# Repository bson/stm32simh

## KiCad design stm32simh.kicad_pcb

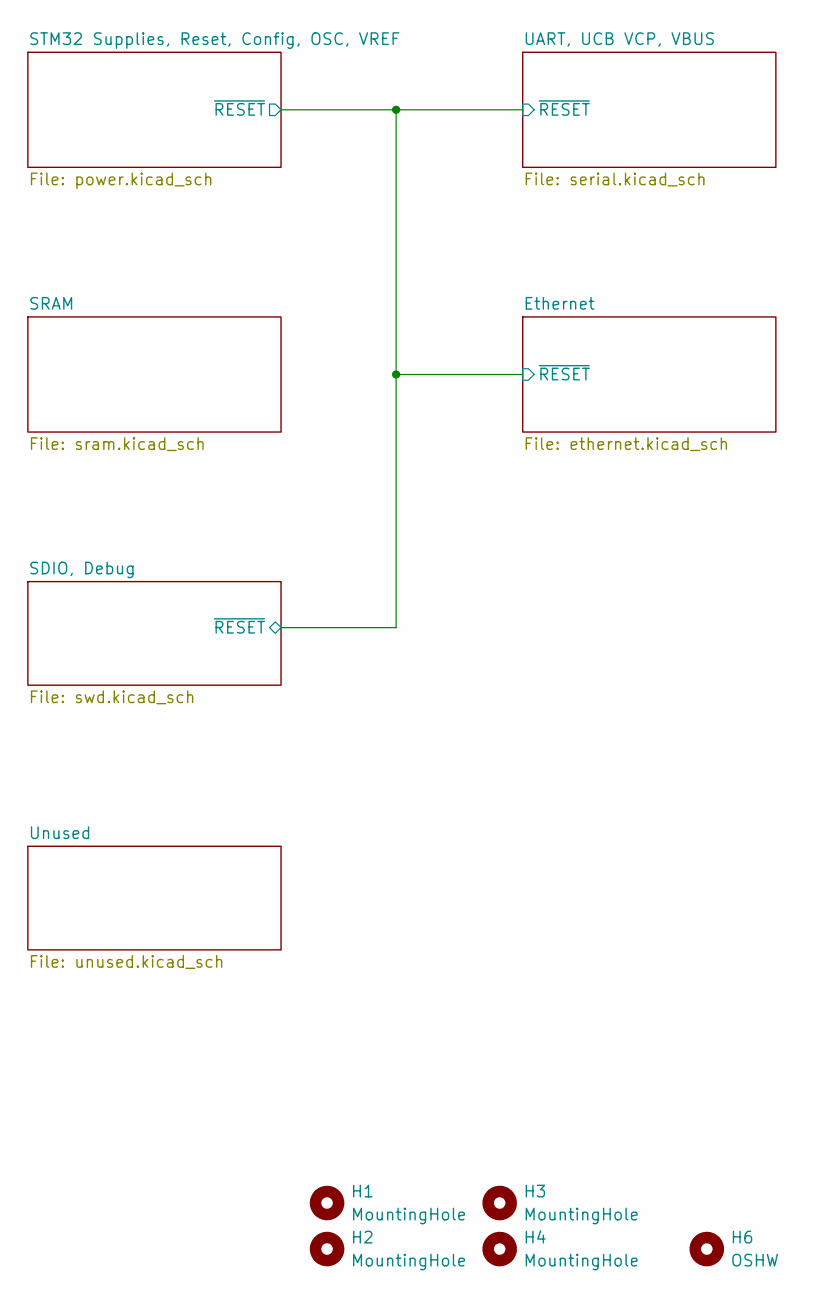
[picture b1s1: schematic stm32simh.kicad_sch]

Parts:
H1, H2, H3, H4: MountingHole; MountingHole_2.2mm_M2_ISO14580_Pad
H6: OSHW; OSHW-Logo_7.5x8mm_SilkScreen

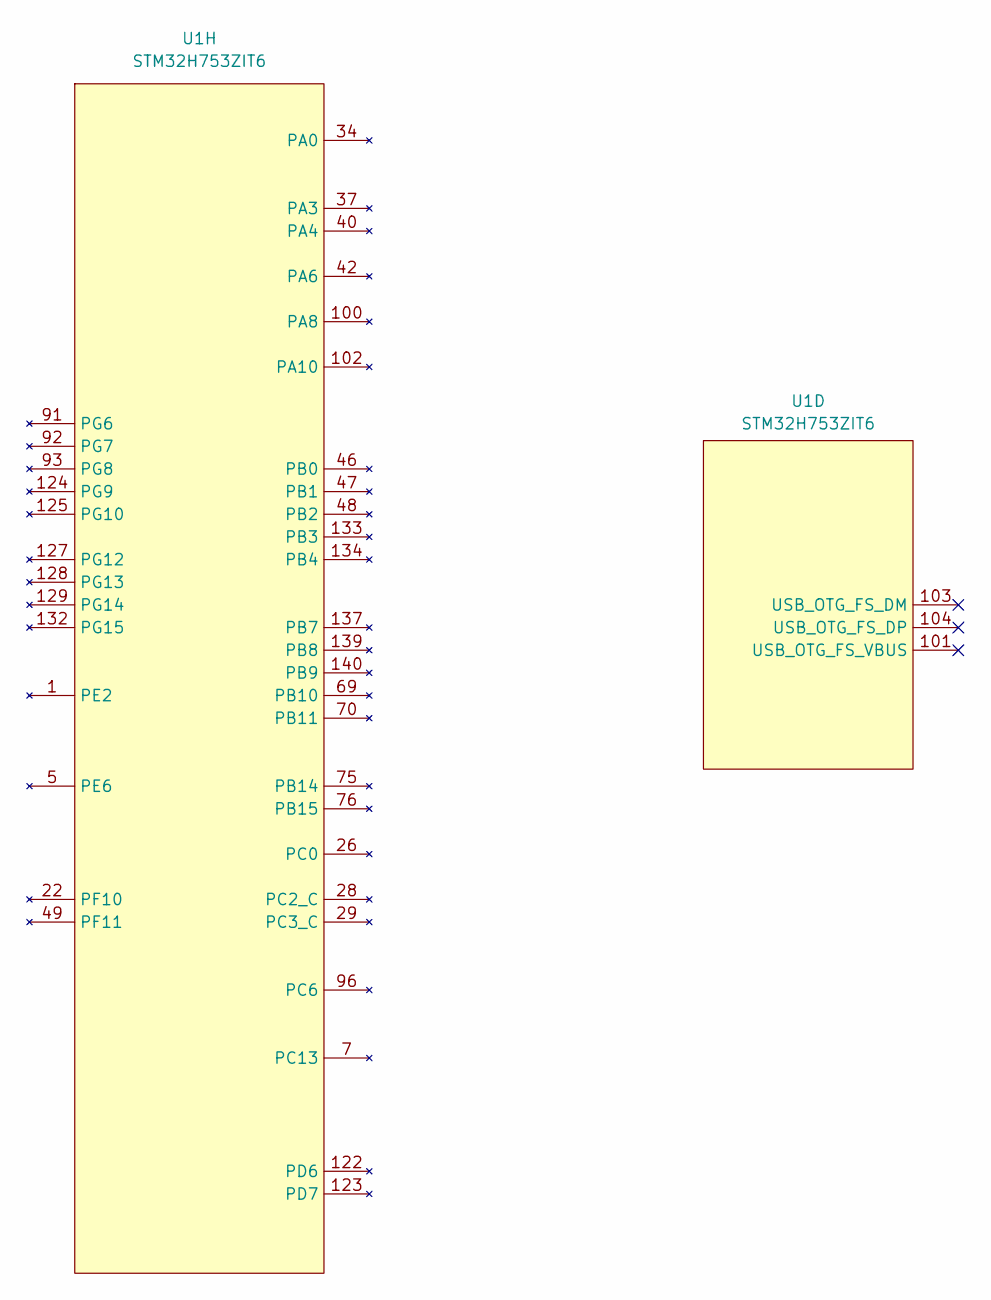
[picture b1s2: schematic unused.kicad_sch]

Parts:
U1: STM32H753ZIT6; LQFP-144_20x20mm_P0.5mm; MPN STM32H753ZIT6

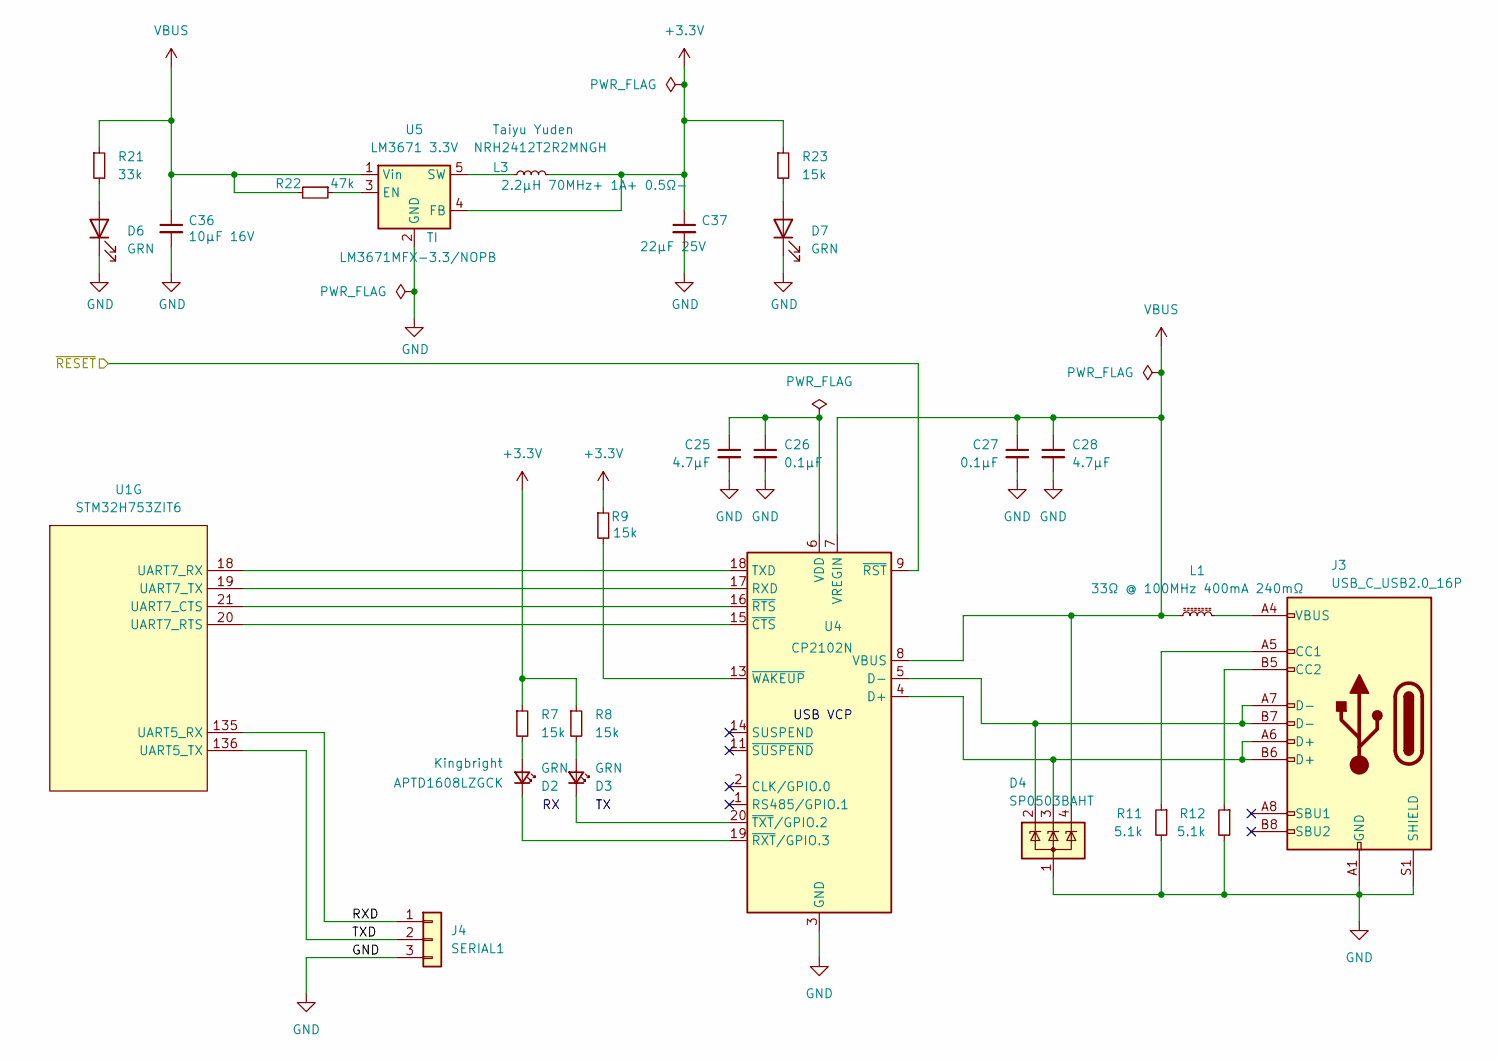
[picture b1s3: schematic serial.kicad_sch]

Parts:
C25, C28: 4.7µF; C_0805_2012Metric; LCSC C84718
C26, C27: 0.1µF; C_0402_1005Metric; LCSC C3012376
C36: 10µF 16V; C_0603_1608Metric; LCSC C109457
C37: 22µF 25V; C_0805_2012Metric; LCSC C258782
D2, D3: GRN; D_0603_1608Metric; MPN APTD1608LZGCK; LCSC C5246833
D4: SP0503BAHT; SOT-143; LCSC C5337181
D6, D7: GRN; D_0603_1608Metric; LCSC C5246833
J3: USB_C_USB2.0_16P; USB_C_Receptacle_HCTL_HC-TYPE-C-16P-01A; LCSC C2909599
J4: SERIAL1; PinHeader_1x03_P2.54mm_Vertical
L1: 33Ω @ 100MHz 400mA 240mΩ; L_0402_1005Metric; MPN MMZ1005D330CTD25
L3: 2.2µH 70MHz+ 1A+ 0.5Ω-; L_Taiyo-Yuden_NR-24xx; Part NRH2412T2R2MNGH
R7, R8, R23: 15k; R_0402_1005Metric; LCSC C850820
R9: 15k; R_0402_1005Metric; LCSC C375970
R11, R12: 5.1k; R_0402_1005Metric; LCSC C384321
R21: 33k; R_0402_1005Metric; LCSC C2906928
R22: 47k; R_0402_1005Metric; LCSC C3017507
U1: STM32H753ZIT6; LQFP-144_20x20mm_P0.5mm; MPN STM32H753ZIT6
U4: CP2102N; CP2102N-QFN20; LCSC C969913
U5: LM3671 3.3V; TSOT-23-5; Part LM3671MFX-3.3/NOPB; LCSC C201586

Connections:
+3.3V: C37.1, L3.2, R7.1, R8.1, R9.1, R23.1, U5.4 (FB); also elsewhere on the board
/Ethernet/~RESET: U4.9 (~RST); also elsewhere on the board
/UART, UCB VCP, VBUS/RXD: J4.1, U1.135 (UART5_RX)
/UART, UCB VCP, VBUS/TXD: J4.2, U1.136 (UART5_TX)
GND: C25.2, C26.2, C27.2, C28.2, C36.2, C37.2, D4.1 (A), D6.1 (K), D7.1 (K), J3.A1 (GND), J3.A12 (GND), J3.B1 (GND), J3.B12 (GND), J3.S1 (SHIELD), J4.3, R11.2, R12.2, U4.3 (GND), U4.12 (GND), U4.21 (GND), U5.2 (GND); also elsewhere on the board
unnamed: D2.2 (A), R7.2
unnamed: D2.1 (K), U4.19 (~RXT/GPIO.3)
unnamed: D3.2 (A), R8.2
unnamed: D3.1 (K), U4.20 (~TXT/GPIO.2)
unnamed: D6.2 (A), R21.2
unnamed: D7.2 (A), R23.2
unnamed: J3.A5 (CC1), R11.1
unnamed: J3.B5 (CC2), R12.1
unnamed: J3.A4 (VBUS), J3.A9 (VBUS), J3.B4 (VBUS), J3.B9 (VBUS), L1.2
unnamed: U1.21 (UART7_CTS), U4.16 (~RTS)
unnamed: U1.20 (UART7_RTS), U4.15 (~CTS)
unnamed: U1.18 (UART7_RX), U4.18 (TXD)
unnamed: U1.19 (UART7_TX), U4.17 (RXD)
unnamed: D4.3 (K), J3.A6 (D+), J3.B6 (D+), U4.4 (D+)
unnamed: D4.2 (K), J3.A7 (D-), J3.B7 (D-), U4.5 (D-)
unnamed: C25.1, C26.1, U4.6 (VDD)
unnamed: R9.2, U4.13 (~WAKEUP)
unnamed: R22.1, U5.3 (EN)
unnamed: L3.1, U5.5 (SW)
VBUS: C27.1, C28.1, C36.1, D4.4 (K), L1.1, R21.1, R22.2, U4.7 (VREGIN), U4.8 (VBUS), U5.1 (Vin)

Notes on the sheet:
USB VCP

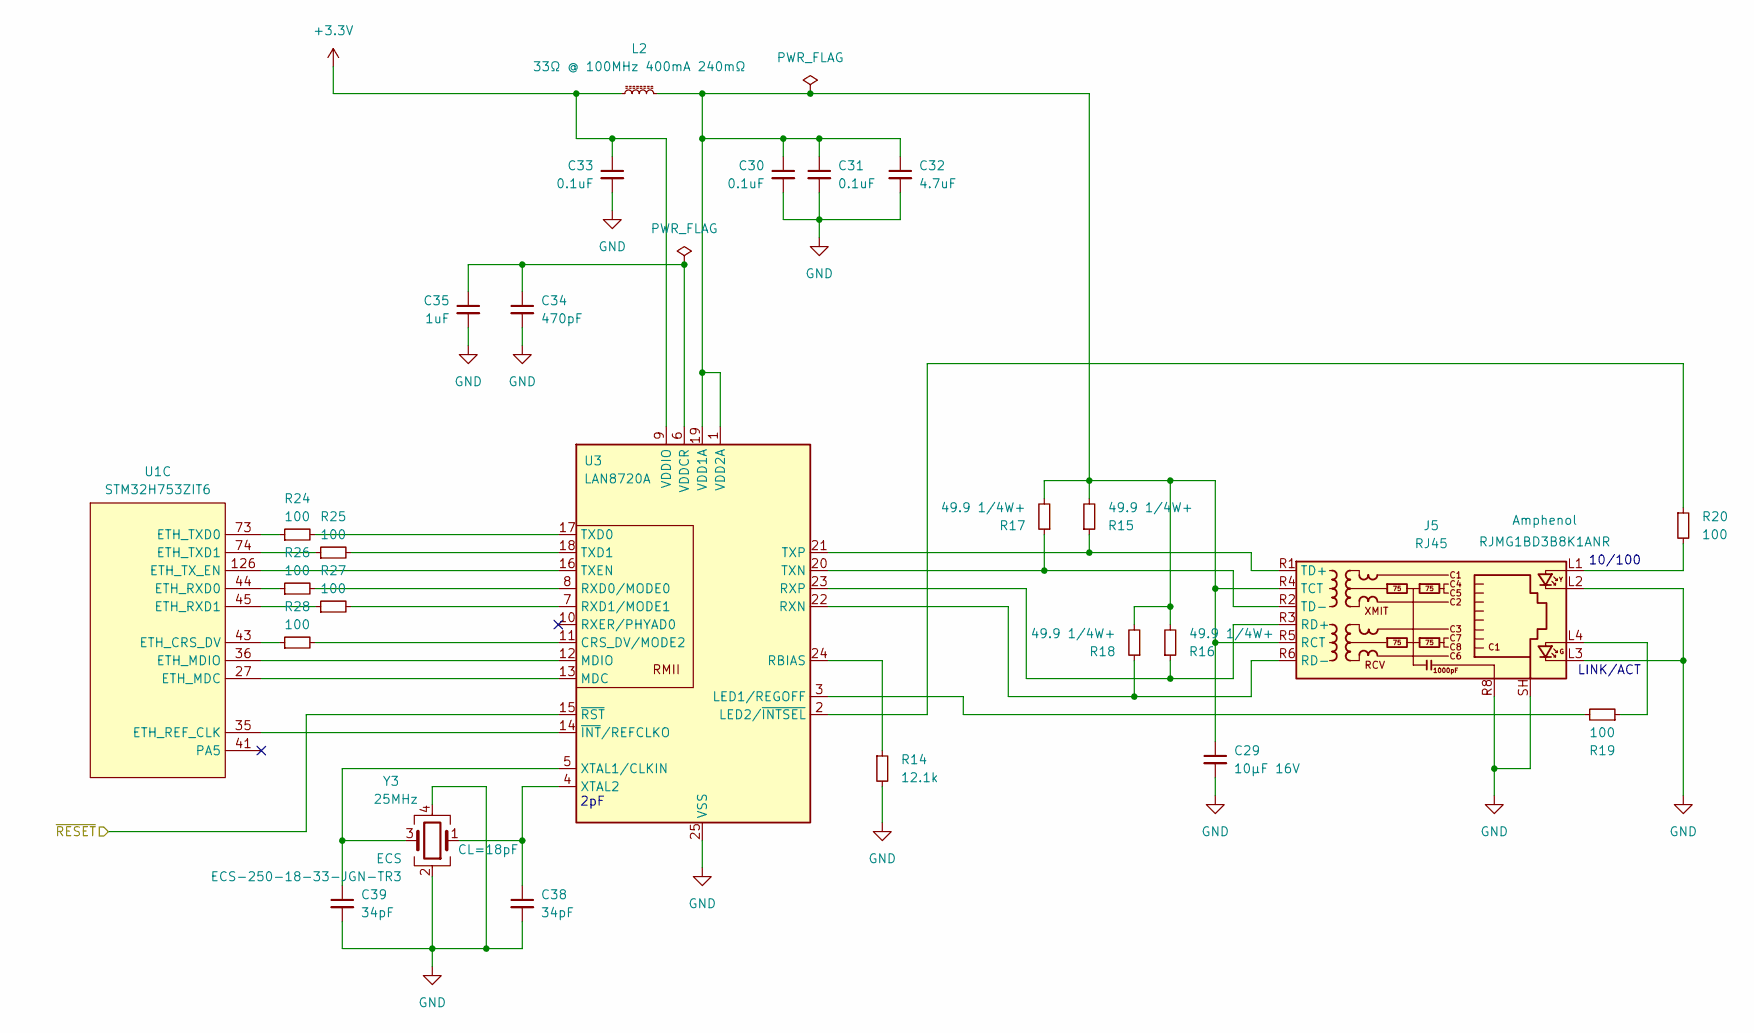
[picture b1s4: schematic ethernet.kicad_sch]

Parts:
C29: 10µF 16V; C_0603_1608Metric; LCSC C109457
C30, C31, C33: 0.1uF; C_0402_1005Metric
C32: 4.7uF; C_0805_2012Metric
C34: 470pF; C_0402_1005Metric
C35: 1uF; C_0402_1005Metric
C38, C39: 34pF; C_0402_1005Metric
J5: RJ45; RJ45_Amphenol_RJMG1BD3B8K1ANR; Part RJMG1BD3B8K1ANR
L2: 33Ω @ 100MHz 400mA 240mΩ; L_0402_1005Metric; MPN MMZ1005D330CTD25
R14: 12.1k; R_0402_1005Metric
R15, R16, R17, R18: 49.9 1/4W+; R_0805_2012Metric; LCSC C4088942
R19, R20, R24, R25, R26, R27, R28: 100; R_0402_1005Metric; LCSC C453594
U1: STM32H753ZIT6; LQFP-144_20x20mm_P0.5mm; MPN STM32H753ZIT6
U3: LAN8720A; VQFN-24-1EP_4x4mm_P0.5mm_EP2.5x2.5mm
Y3: 25MHz; Crystal_SMD_3225-4Pin_3.2x2.5mm; Part ECS-250-18-33-JGN-TR3; LCSC C7294571

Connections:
+3.3V: C33.1, L2.1, U3.9 (VDDIO); also elsewhere on the board
/Ethernet/~RESET: U3.15 (~RST); also elsewhere on the board
GND: C29.2, C30.2, C31.2, C32.2, C33.2, C34.2, C35.2, C38.2, C39.2, J5.L2, J5.L3, J5.R8, J5.SH, R14.2, U3.25 (VSS), Y3.2, Y3.4; also elsewhere on the board
unnamed: J5.L1, R20.2
unnamed: J5.L4, R19.1
unnamed: C29.1, C30.1, C31.1, C32.1, J5.R4 (TCT), J5.R5 (RCT), L2.2, R15.2, R16.2, R17.2, R18.2, U3.1 (VDD2A), U3.19 (VDD1A)
unnamed: J5.R3 (RD+), R16.1, U3.23 (RXP)
unnamed: J5.R6 (RD-), R18.1, U3.22 (RXN)
unnamed: J5.R1 (TD+), R15.1, U3.21 (TXP)
unnamed: J5.R2 (TD-), R17.1, U3.20 (TXN)
unnamed: R28.1, U1.43 (ETH_CRS_DV)
unnamed: U1.27 (ETH_MDC), U3.13 (MDC)
unnamed: U1.36 (ETH_MDIO), U3.12 (MDIO)
unnamed: U1.35 (ETH_REF_CLK), U3.14 (~INT/REFCLKO)
unnamed: R26.1, U1.44 (ETH_RXD0)
unnamed: R27.1, U1.45 (ETH_RXD1)
unnamed: R24.1, U1.73 (ETH_TXD0)
unnamed: R25.1, U1.74 (ETH_TXD1)
unnamed: U1.126 (ETH_TX_EN), U3.16 (TXEN)
unnamed: R28.2, U3.11 (CRS_DV/MODE2)
unnamed: R19.2, U3.3 (LED1/REGOFF)
unnamed: R20.1, U3.2 (LED2/~INTSEL)
unnamed: R14.1, U3.24 (RBIAS)
unnamed: R26.2, U3.8 (RXD0/MODE0)
unnamed: R27.2, U3.7 (RXD1/MODE1)
unnamed: R24.2, U3.17 (TXD0)
unnamed: R25.2, U3.18 (TXD1)
unnamed: C34.1, C35.1, U3.6 (VDDCR)
unnamed: C39.1, U3.5 (XTAL1/CLKIN), Y3.3
unnamed: C38.1, U3.4 (XTAL2), Y3.1

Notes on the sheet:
LINK/ACT
2pF
10/100

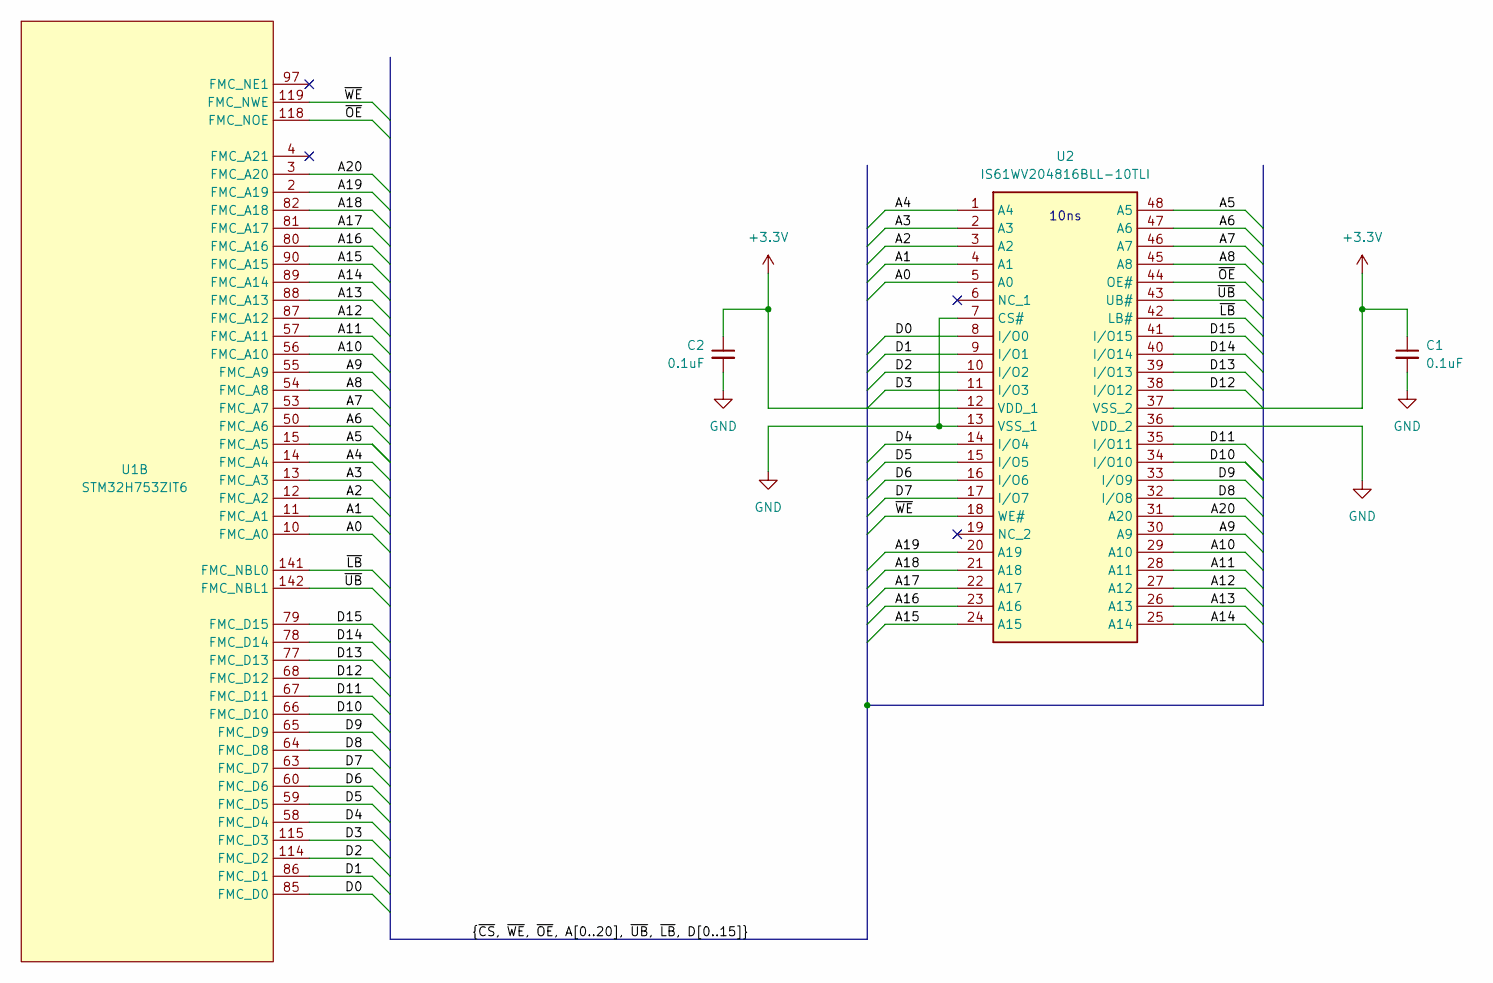
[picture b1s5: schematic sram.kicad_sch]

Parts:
C1, C2: 0.1uF; C_0402_1005Metric
U1: STM32H753ZIT6; LQFP-144_20x20mm_P0.5mm; MPN STM32H753ZIT6
U2: IS61WV204816BLL-10TLI; SOP50P2000X120-48N; Mouser Part Number 870-WV204816BLL10TLI

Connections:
+3.3V: C1.1, C2.1, U2.12 (VDD_1), U2.37 (VSS_2); also elsewhere on the board
/SRAM/A0: U1.10 (FMC_A0), U2.5 (A0)
/SRAM/A1: U1.11 (FMC_A1), U2.4 (A1)
/SRAM/A2: U1.12 (FMC_A2), U2.3 (A2)
/SRAM/A3: U1.13 (FMC_A3), U2.2 (A3)
/SRAM/A4: U1.14 (FMC_A4), U2.1 (A4)
/SRAM/A5: U1.15 (FMC_A5), U2.48 (A5)
/SRAM/A6: U1.50 (FMC_A6), U2.47 (A6)
/SRAM/A7: U1.53 (FMC_A7), U2.46 (A7)
/SRAM/A8: U1.54 (FMC_A8), U2.45 (A8)
/SRAM/A9: U1.55 (FMC_A9), U2.30 (A9)
/SRAM/A10: U1.56 (FMC_A10), U2.29 (A10)
/SRAM/A11: U1.57 (FMC_A11), U2.28 (A11)
/SRAM/A12: U1.87 (FMC_A12), U2.27 (A12)
/SRAM/A13: U1.88 (FMC_A13), U2.26 (A13)
/SRAM/A14: U1.89 (FMC_A14), U2.25 (A14)
/SRAM/A15: U1.90 (FMC_A15), U2.24 (A15)
/SRAM/A16: U1.80 (FMC_A16), U2.23 (A16)
/SRAM/A17: U1.81 (FMC_A17), U2.22 (A17)
/SRAM/A18: U1.82 (FMC_A18), U2.21 (A18)
/SRAM/A19: U1.2 (FMC_A19), U2.20 (A19)
/SRAM/A20: U1.3 (FMC_A20), U2.31 (A20)
/SRAM/D0: U1.85 (FMC_D0), U2.8 (I/O0)
/SRAM/D1: U1.86 (FMC_D1), U2.9 (I/O1)
/SRAM/D2: U1.114 (FMC_D2), U2.10 (I/O2)
/SRAM/D3: U1.115 (FMC_D3), U2.11 (I/O3)
/SRAM/D4: U1.58 (FMC_D4), U2.14 (I/O4)
/SRAM/D5: U1.59 (FMC_D5), U2.15 (I/O5)
/SRAM/D6: U1.60 (FMC_D6), U2.16 (I/O6)
/SRAM/D7: U1.63 (FMC_D7), U2.17 (I/O7)
/SRAM/D8: U1.64 (FMC_D8), U2.32 (I/O8)
/SRAM/D9: U1.65 (FMC_D9), U2.33 (I/O9)
/SRAM/D10: U1.66 (FMC_D10), U2.34 (I/O10)
/SRAM/D11: U1.67 (FMC_D11), U2.35 (I/O11)
/SRAM/D12: U1.68 (FMC_D12), U2.38 (I/O12)
/SRAM/D13: U1.77 (FMC_D13), U2.39 (I/O13)
/SRAM/D14: U1.78 (FMC_D14), U2.40 (I/O14)
/SRAM/D15: U1.79 (FMC_D15), U2.41 (I/O15)
/SRAM/~LB: U1.141 (FMC_NBL0), U2.42 (LB#)
/SRAM/~OE: U1.118 (FMC_NOE), U2.44 (OE#)
/SRAM/~UB: U1.142 (FMC_NBL1), U2.43 (UB#)
/SRAM/~WE: U1.119 (FMC_NWE), U2.18 (WE#)
GND: C1.2, C2.2, U2.7 (CS#), U2.13 (VSS_1), U2.36 (VDD_2); also elsewhere on the board

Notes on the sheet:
10ns

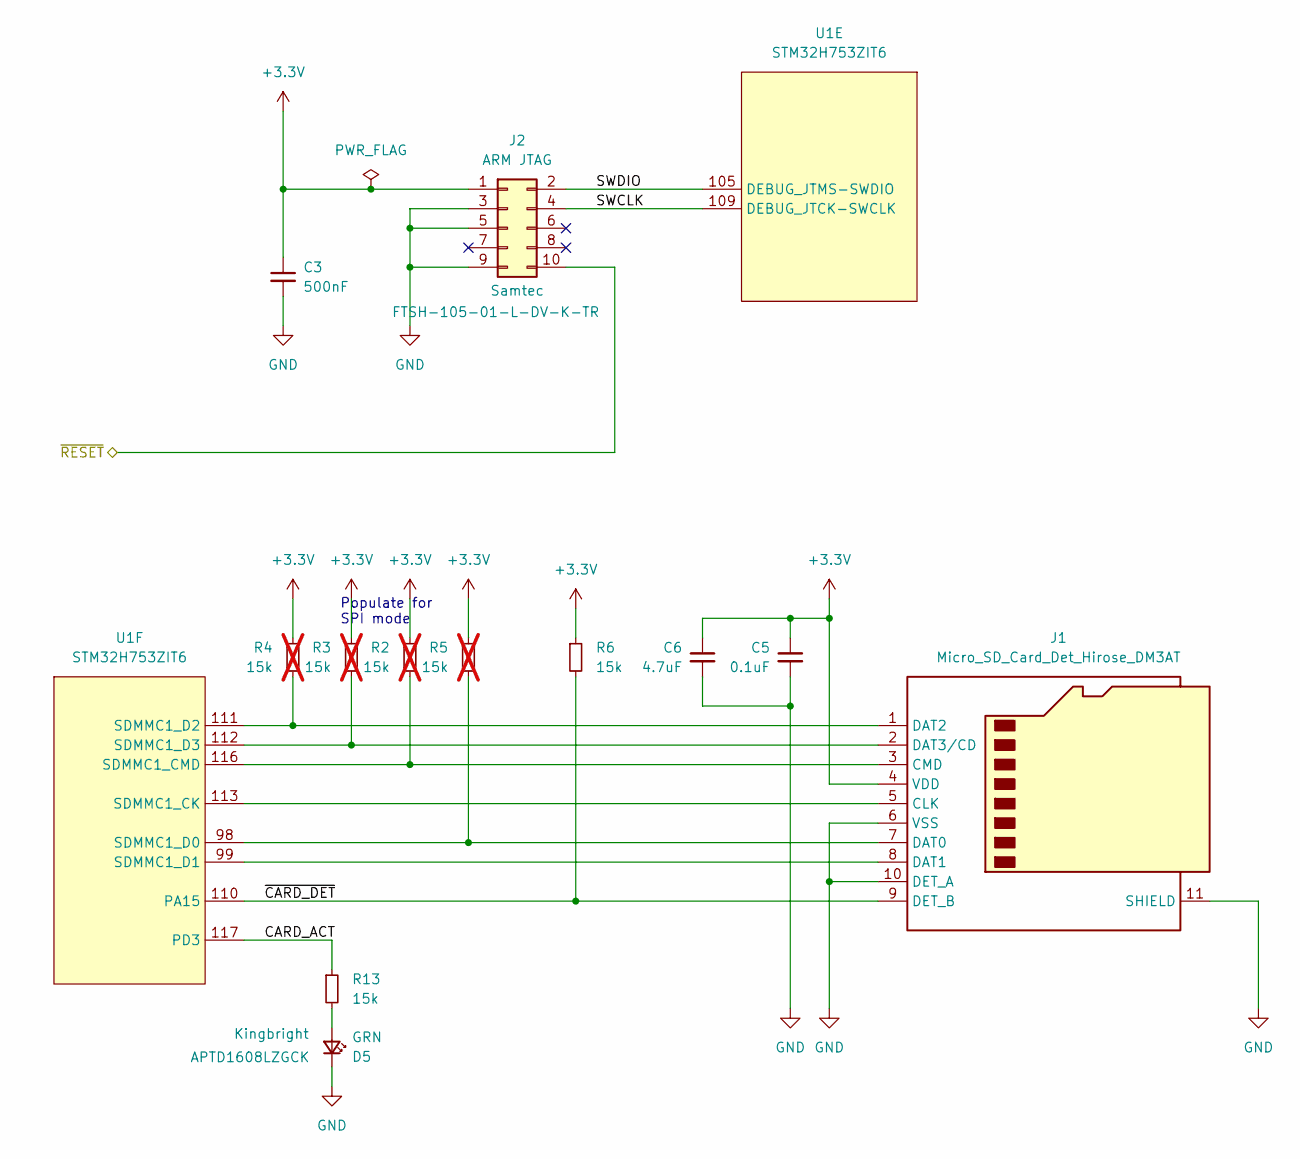
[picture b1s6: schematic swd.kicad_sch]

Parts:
C3: 500nF; C_0402_1005Metric
C5: 0.1uF; C_0402_1005Metric
C6: 4.7uF; C_0805_2012Metric
D5: GRN; D_0603_1608Metric; MPN APTD1608LZGCK; LCSC C5246833
J1: Micro_SD_Card_Det_Hirose_DM3AT; microSD_HC_Hirose_DM3AT-SF-PEJM5
J2: ARM JTAG; SOIC-10_3.9x4.9mm_P1mm; MPN FTSH-105-01-L-DV-K-TR
R2, R3, R4, R5: 15k; R_0402_1005Metric; not fitted
R6: 15k; R_0402_1005Metric
R13: 15k; R_0402_1005Metric; LCSC C850820
U1: STM32H753ZIT6; LQFP-144_20x20mm_P0.5mm; MPN STM32H753ZIT6

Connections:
+3.3V: C3.1, C5.1, C6.1, J1.4 (VDD), J2.1, R2.1, R3.1, R4.1, R5.1, R6.1; also elsewhere on the board
/Ethernet/~RESET: J2.10; also elsewhere on the board
/SDIO, Debug/CARD_ACT: R13.1, U1.117 (PD3)
/SDIO, Debug/SWCLK: J2.4, U1.109 (DEBUG_JTCK-SWCLK)
/SDIO, Debug/SWDIO: J2.2, U1.105 (DEBUG_JTMS-SWDIO)
/SDIO, Debug/~CARD_DET: J1.9 (DET_B), R6.2, U1.110 (PA15)
GND: C3.2, C5.2, C6.2, D5.1 (K), J1.6 (VSS), J1.10 (DET_A), J1.11 (SHIELD), J2.3, J2.5, J2.9; also elsewhere on the board
unnamed: D5.2 (A), R13.2
unnamed: J1.5 (CLK), U1.113 (SDMMC1_CK)
unnamed: J1.3 (CMD), R2.2, U1.116 (SDMMC1_CMD)
unnamed: J1.7 (DAT0), R5.2, U1.98 (SDMMC1_D0)
unnamed: J1.8 (DAT1), U1.99 (SDMMC1_D1)
unnamed: J1.1 (DAT2), R4.2, U1.111 (SDMMC1_D2)
unnamed: J1.2 (DAT3/CD), R3.2, U1.112 (SDMMC1_D3)

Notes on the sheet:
Populate for SPI mode

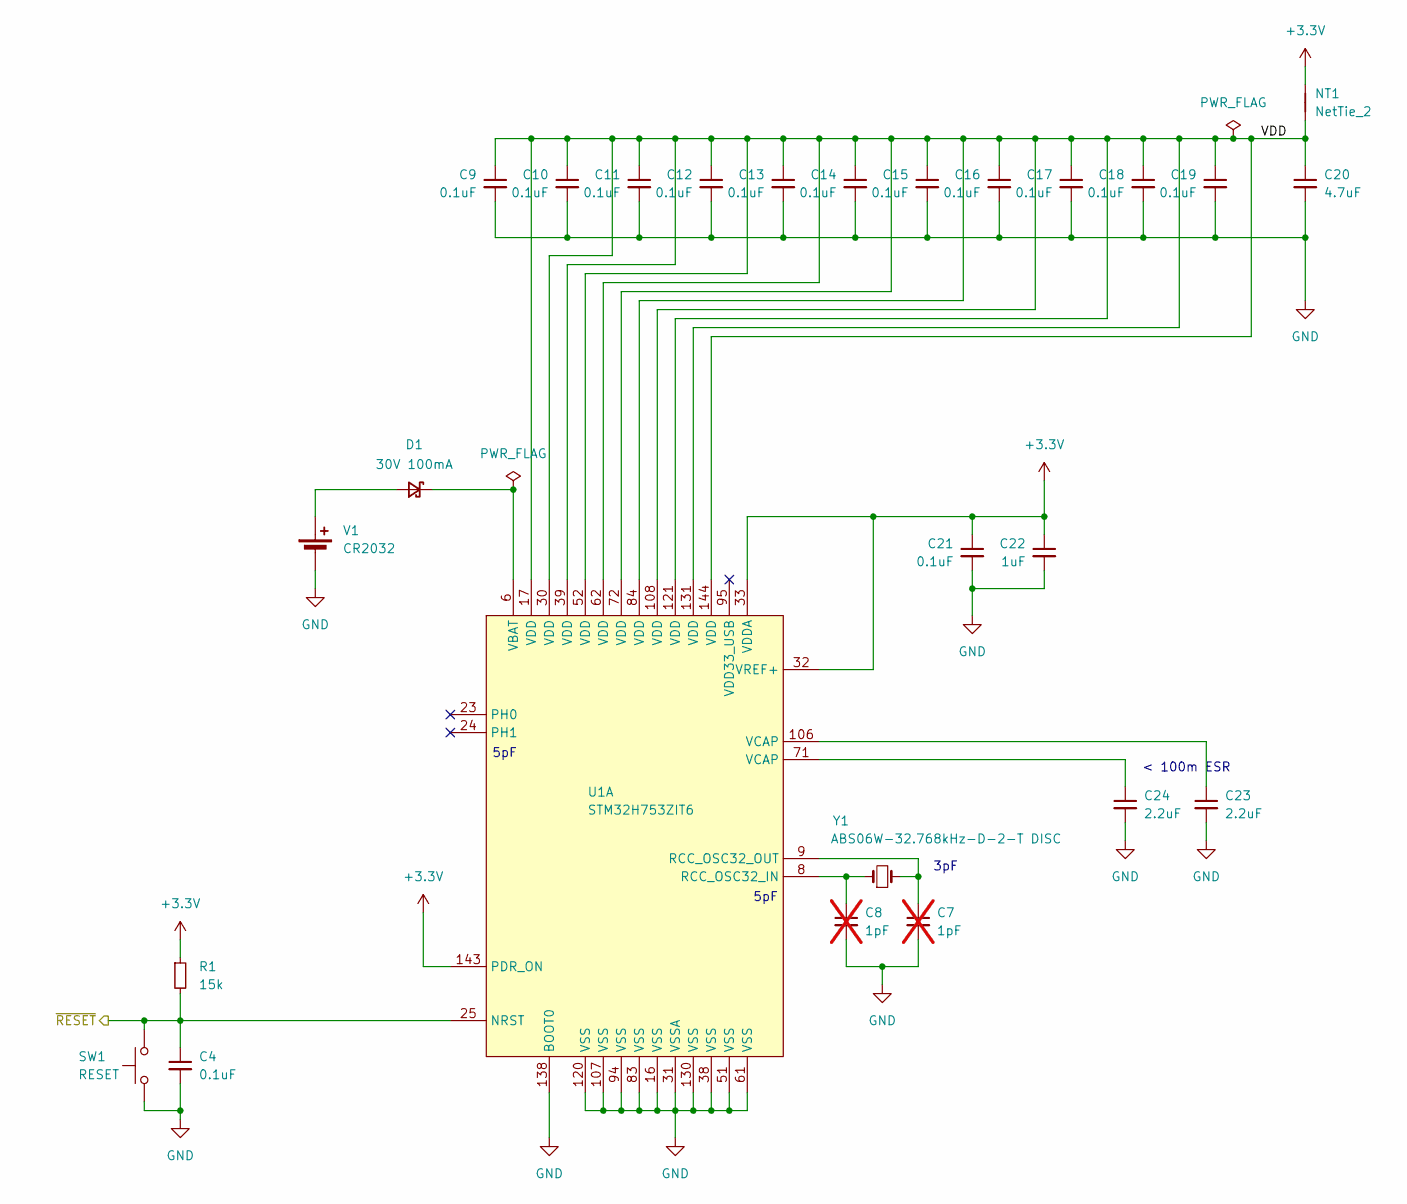
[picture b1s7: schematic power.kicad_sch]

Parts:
C4, C9, C10, C11, C12, C13, C14, C15, C16, C17, C18, C19, C21: 0.1uF; C_0402_1005Metric
C7, C8: 1pF; C_0402_1005Metric; not fitted
C20: 4.7uF; C_0805_2012Metric
C22: 1uF; C_0402_1005Metric
C23, C24: 2.2uF; C_0603_1608Metric
D1: 30V 100mA; D_0603_1608Metric; MPN CDBU0130L-HF
NT1: NetTie_2; NetTie-2_SMD_Pad0.5mm
R1: 15k; R_0402_1005Metric
SW1: RESET; SW_SPST_CK_RS282G05A3
U1: STM32H753ZIT6; LQFP-144_20x20mm_P0.5mm; MPN STM32H753ZIT6
V1: CR2032; BatteryHolder_Keystone_1060_1x2032; MPN 1060TR
Y1: ABS06W-32.768kHz-D-2-T DISC; Crystal_SMD_2012-2Pin_2.0x1.2mm; MPN ABS06W-32.768KHZ-D-2-T

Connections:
+3.3V: C21.1, C22.1, NT1.2, R1.1, U1.32 (VREF+), U1.33 (VDDA), U1.143 (PDR_ON); also elsewhere on the board
/Ethernet/~RESET: C4.1, R1.2, SW1.1, U1.25 (NRST); also elsewhere on the board
/STM32 Supplies, Reset, Config, OSC, VREF/VDD: C9.1, C10.1, C11.1, C12.1, C13.1, C14.1, C15.1, C16.1, C17.1, C18.1, C19.1, C20.1, NT1.1, U1.17 (VDD), U1.30 (VDD), U1.39 (VDD), U1.52 (VDD), U1.62 (VDD), U1.72 (VDD), U1.84 (VDD), U1.108 (VDD), U1.121 (VDD), U1.131 (VDD), U1.144 (VDD)
GND: C4.2, C7.2, C8.2, C9.2, C10.2, C11.2, C12.2, C13.2, C14.2, C15.2, C16.2, C17.2, C18.2, C19.2, C20.2, C21.2, C22.2, C23.2, C24.2, SW1.2, U1.16 (VSS), U1.31 (VSSA), U1.38 (VSS), U1.51 (VSS), U1.61 (VSS), U1.83 (VSS), U1.94 (VSS), U1.107 (VSS), U1.120 (VSS), U1.130 (VSS), U1.138 (BOOT0), V1.2 (-); also elsewhere on the board
unnamed: C23.1, U1.106 (VCAP)
unnamed: C24.1, U1.71 (VCAP)
unnamed: D1.2 (A), V1.1 (+)
unnamed: D1.1 (K), U1.6 (VBAT)
unnamed: C8.1, U1.8 (RCC_OSC32_IN), Y1.1
unnamed: C7.1, U1.9 (RCC_OSC32_OUT), Y1.2

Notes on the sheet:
5pF
3pF
< 100m ESR

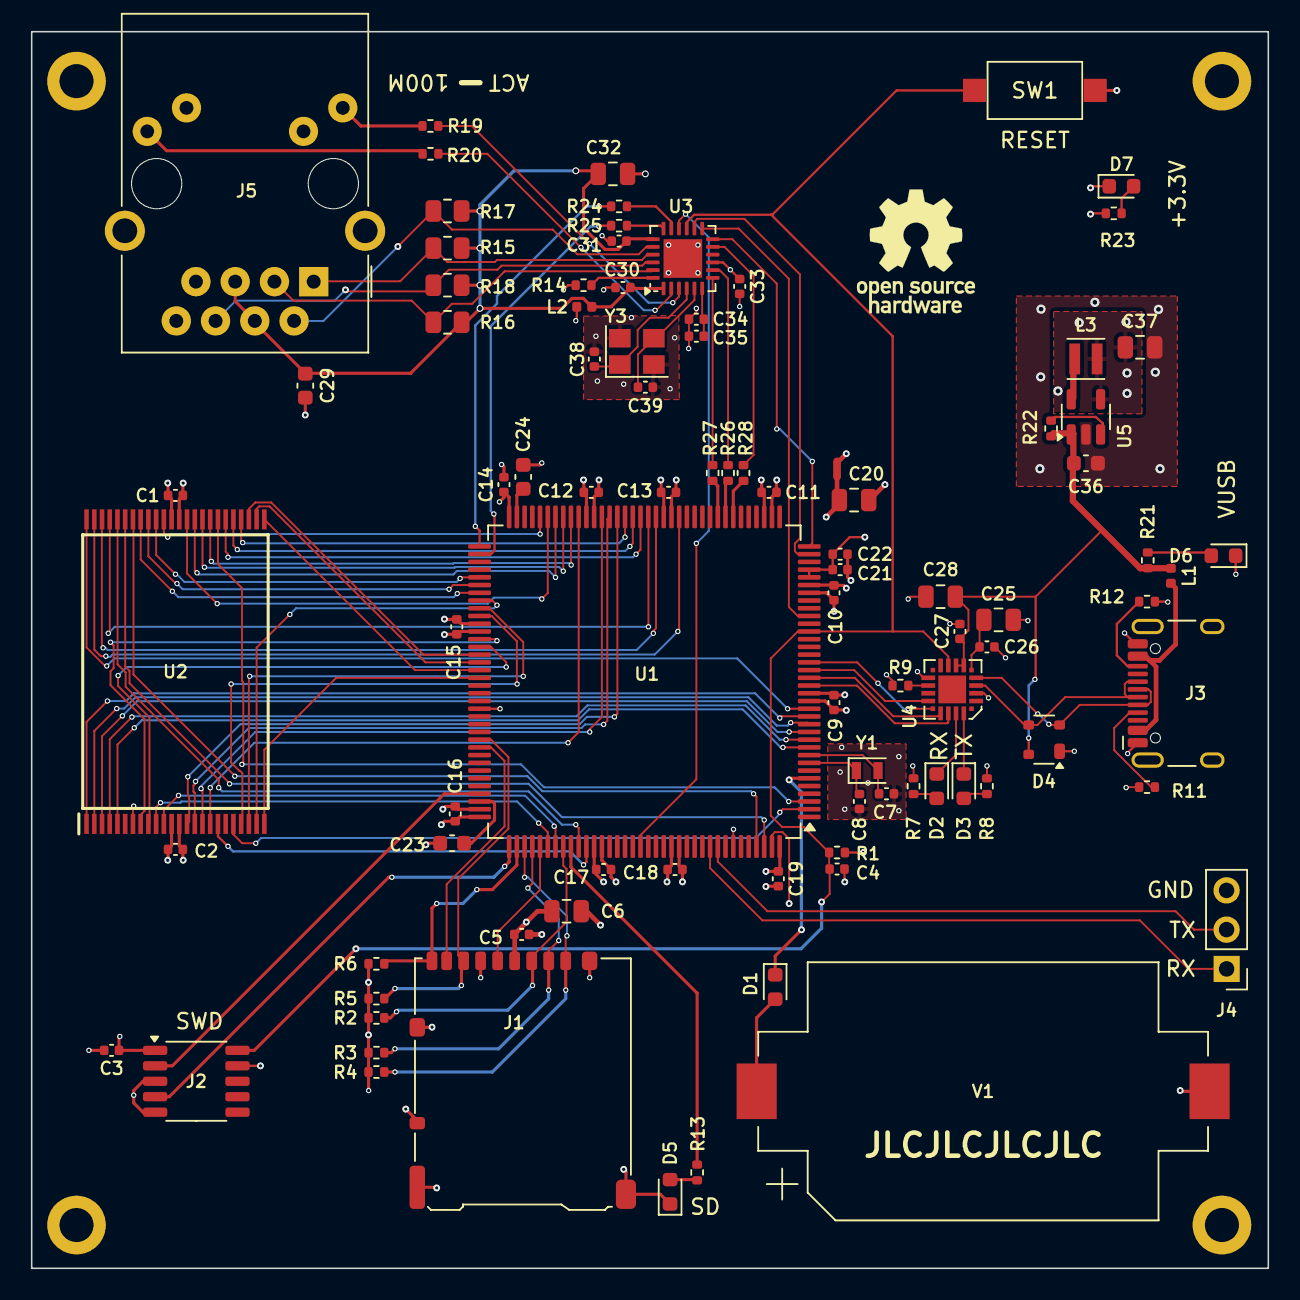
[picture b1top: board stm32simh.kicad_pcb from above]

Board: 4 copper layers, 80.0 x 80.0 mm, 96 parts (0 on the bottom side), 111 nets.

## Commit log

2024-10-08 checkpoint
2024-10-08 add reset button
2024-10-08 cleanups
2024-10-08 add SDIO
2024-10-08 first stab at board layout
2024-10-08 VDD zone
2024-10-08 add a bunch of files
2024-10-08 align holes
2024-10-08 remove unused footprint
2024-10-09 add rev1 gerbers
2025-09-15 update to KiCad 9, add ibom
